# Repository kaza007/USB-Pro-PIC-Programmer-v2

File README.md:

# USB-Pro-PIC-Programmer-v2
OshonSoft Compatible USB PIC Programmer

Background
----------
The USB Pro PIC-PIC18-PIC16-AVR programmer is an [*open project*](http://www.oshonsoft.com/picprogprousb.html) created by Vladimir Soso, the author of the PIC Simulator IDE at [*OshonSoft.com*](http://www.oshonsoft.com/).

This project is a PCB for the USB Pro PIC Programmer with added DC-DC converter. The programmer can now be powered by the USB port without the use of an external power supply. The PCB is also very easy to assemble as all the components are *through hole* type.

Design Software
-----------------
This project was designed with [Eagle](http://www.cadsoftusa.com/) 7.2.0, [Sketchup](http://www.sketchup.com/) 15.3.331 and [EagleUp](http://eagleup.wordpress.com) 4.5.

License
-------

This work is licensed under a [Creative Commons Attribution-ShareAlike 4.0 International License](<http://creativecommons.org/licenses/by-sa/4.0/).

Original design by: Vladimir Soso, [*OshonSoft.com*](http://www.oshonsoft.com/).

Modified by: [*https://github.com/kaza007*](https://github.com/kaza007)

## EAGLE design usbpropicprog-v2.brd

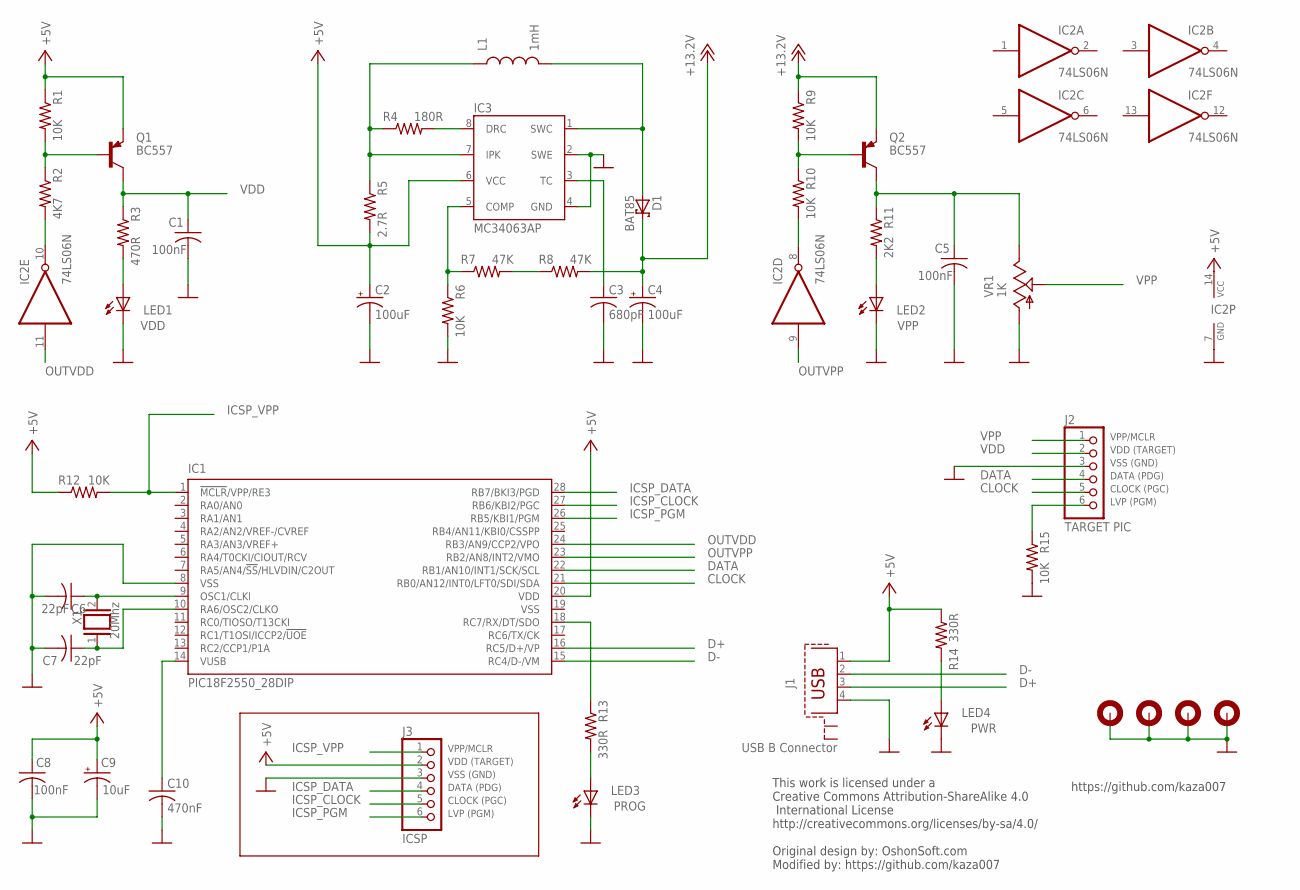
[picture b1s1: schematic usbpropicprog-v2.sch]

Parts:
C1, C5, C8: 100nF; C050-025X075
C2, C4: 100uF; E2,5-6,3
C3: 680pF; C050-025X075
C6, C7: 22pF; C025-024X044
C9: 10uF; E2-5
C10: 470nF; C050-035X075
D1: BAT85; DO41-7.6
H1, H2, H3, H4: MOUNT-PAD-ROUND2.8; 2,8-PAD
IC1: PIC18F2550_28DIP; DIL28-3
IC2: 74LS06N; DIL14
IC3: MC34063AP; DIL-08
J1: USB B Connector; PN61729-S
J2: TARGET PIC; 1X06
J3: ICSP; 1X06
L1: 1mH; RLB0912
LED1: VDD; LED5MM
LED2: VPP; LED5MM
LED3: PROG; LED5MM
LED4: PWR; LED5MM
Q1, Q2: BC557; TO92-EBC
R1, R6, R9, R10, R12, R15: 10K; 0207/10
R2: 4K7; 0207/10
R3: 470R; 0207/10
R4: 180R; 0207/10
R5: 2.7R; 0207/10
R7, R8: 47K; 0207/10
R11: 2K2; 0207/10
R13, R14: 330R; 0207/10
VR1: 1K; R-TRIMMT93YA
X1: 20Mhz; QS

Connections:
+5V: C2.+, C8.1, C9.+, IC1.20 (VDD), IC2.14 (VCC), IC3.6 (VCC), J1.1, J3.2, Q1.E, R1.1, R5.2, R12.1, R14.1
+12V: C4.+, D1.C, Q2.E, R8.2, R9.1
CLOCK: IC1.21 (RB0/AN12/INT0/LFT0/SDI/SDA), J2.5
D+: IC1.16 (RC5/D+/VP), J1.3
D-: IC1.15 (RC4/D-/VM), J1.2
DATA: IC1.22 (RB1/AN10/INT1/SCK/SCL), J2.4
GND: C1.2, C2.-, C3.2, C4.-, C5.2, C6.2, C7.2, C8.2, C9.-, C10.2, H1.B2,8, H2.B2,8, H3.B2,8, H4.B2,8, IC1.8 (VSS), IC2.7 (GND), IC3.2 (SWE), IC3.4 (GND), J1.4, J2.3, J3.3, LED1.K (C), LED2.K (C), LED3.K (C), LED4.K (C), R6.2, R15.2, VR1.3 (A)
ICSP_CLOCK: IC1.27 (RB6/KBI2/PGC), J3.5
ICSP_DATA: IC1.28 (RB7/BKI3/PGD), J3.4
ICSP_PGM: IC1.26 (RB5/KBI1/PGM), J3.6
ICSP_VPP: IC1.1 (!MCLR!/VPP/RE3), J3.1, R12.2
unnamed: IC1.18 (RC7/RX/DT/SDO), R13.1
unnamed: LED3.A, R13.2
unnamed: R7.2, R8.1
unnamed: J2.6, R15.1
unnamed: LED4.A, R14.2
unnamed: Q1.B, R1.2, R2.1
unnamed: Q2.B, R9.2, R10.1
unnamed: IC3.8 (DRC), R4.2
unnamed: LED1.A, R3.2
unnamed: IC3.7 (IPK), L1.1, R4.1, R5.1
unnamed: IC2.10 (O), R2.2
unnamed: LED2.A, R11.2
unnamed: C6.1, IC1.9 (OSC1/CLKI), X1.2
unnamed: C10.1, IC1.14 (VUSB)
unnamed: IC2.8 (O), R10.2
unnamed: D1.A, IC3.1 (SWC), L1.2
unnamed: C3.1, IC3.3 (TC)
unnamed: IC3.5 (COMP), R6.1, R7.1
unnamed: C7.1, IC1.10 (RA6/OSC2/CLKO), X1.1
OUTVDD: IC1.24 (RB3/AN9/CCP2/VPO), IC2.11 (I)
OUTVPP: IC1.23 (RB2/AN8/INT2/VMO), IC2.9 (I)
VDD: C1.1, J2.2, Q1.C, R3.1
VPP: J2.1, VR1.2 (S)
VPPHIGH: C5.1, Q2.C, R11.1, VR1.1 (E)
VSS: IC1.19 (VSS)

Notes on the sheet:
VPP/MCLR
VDD (TARGET)
VSS (GND)
DATA (PDG)
CLOCK (PGC)
LVP (PGM)
https://github.com/kaza007
This work is licensed under a Creative Commons Attribution-ShareAlike 4.0 International License http://creativecommons.org/licenses/by-sa/4.0/ Original design by: OshonSoft.com Modified by: https://github.com/kaza007

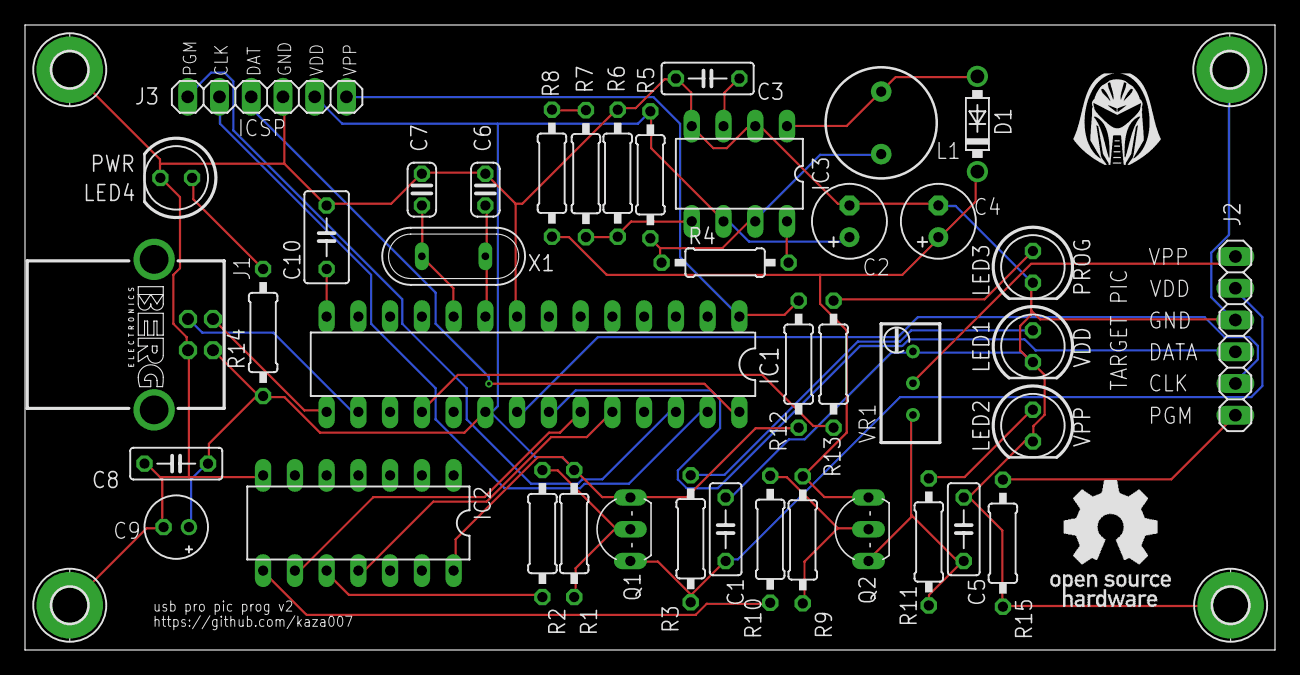
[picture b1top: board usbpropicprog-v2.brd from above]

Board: 2 copper layers, 100.0 x 50.0 mm, 45 parts (0 on the bottom side), 35 nets.

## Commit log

2015-05-29 :lollipop: Added .gitattributes & .gitignore files
2015-05-29 added to readme.md
2015-05-30 add image
2015-05-30 add another image
2015-05-31 removed DXF file reference.
2015-05-31 added easy assembly note

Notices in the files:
parts and their libraries:
kaza007: Licensing: CC v3.0 Share-Alike You are welcome to use this library for commercial purposes.
